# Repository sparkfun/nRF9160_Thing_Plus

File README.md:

SparkFun nRF9160 Thing Plus
========================================

[*SparkFun nRF9160 Thing Plus (17354)*](https://www.sparkfun.com/products/17354)

SparkFun has paired up with CircuitDojo to bring you the SparkFun nRF9160 Thing Plus, which features the powerful Nordic nRF9160 microcontroller in a feather-compatible footprint. This little chip is capable of both CAT M1 LTE and NB-IoT cellular communication and is designed to work with Zephyr, the go-to RTOS for embedded development.

Not only can you take advantage of Nordic’s advanced power states, but you can also put the device into a low power standby state. Laboratory measurements are putting that mode at about 2µA of current. 2µA! It also features a 3.3V Buck-Boost which helps get every mWh from your batteries as possible.

No batteries? No problem! You can plug or power your nRF9160 Thing Plus externally for AC/DC powered operation. Keep it on at all times for high availability scenarios. Power it the 5V pin or insert a micro-USB cable to keep things going.

Want to persist data? The nRF9160 Thing Plus has a 4MB external flash for storing data while offline. Using external flash with a filesystem like LitteFS and you’ll have a project to recon with!

Repository Contents
-------------------

* **/Hardware** - Eagle design files (.brd, .sch)
* **/Production** - Production panel files (.brd)

Documentation
--------------
* **[Hookup Guide](https://learn.sparkfun.com/tutorials/nrf9160-thing-plus-hookup-guide)** - Basic hookup guide for the SparkFun nRF9160 Thing Plus.

License Information
-------------------

This product is _**open source**_! 

Please review the LICENSE.md file for license information. 

If you have any questions or concerns on licensing, please contact technical support on our [SparkFun forums](https://forum.sparkfun.com/viewforum.php?f=152).

Distributed as-is; no warranty is given.

- Your friends at SparkFun.

_Designed in collaboration with [Jared Wolff](https://www.jaredwolff.com/) over at Circuit Dojo._

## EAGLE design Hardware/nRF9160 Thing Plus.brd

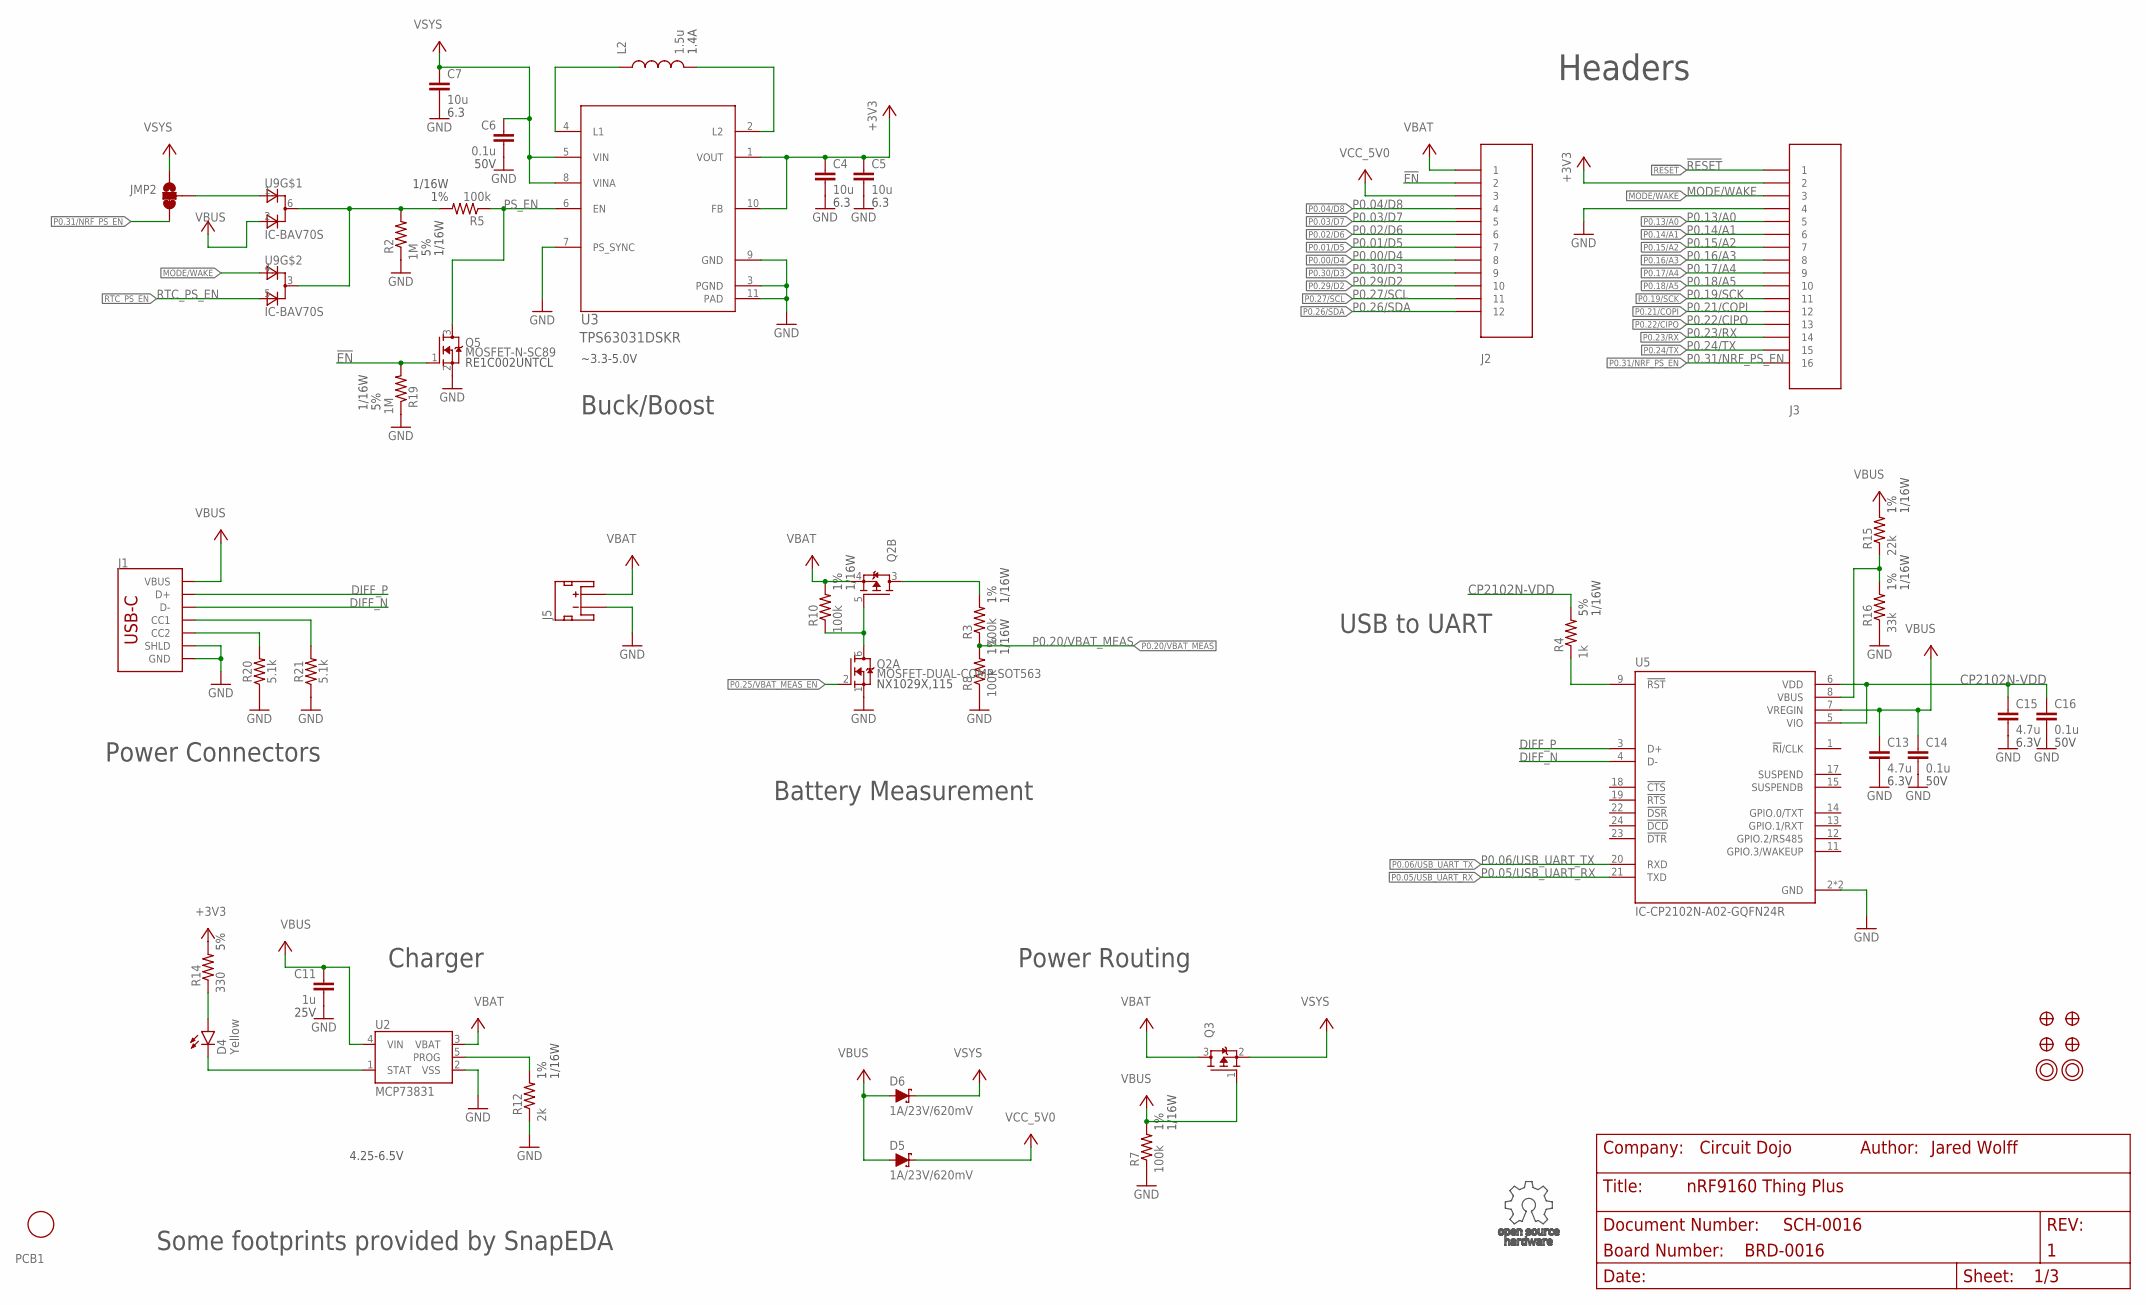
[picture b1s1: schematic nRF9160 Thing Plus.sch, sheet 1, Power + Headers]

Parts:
C4, C5, C7: 10u; C0603
C6, C14, C16: 0.1u; CAPC1005X55N
C11: 1u; CAPC1005X55N
C13, C15: 4.7u; C0603
D4: Yellow; LED-0603
D5, D6: 1A/23V/620mV; SOD-323
J1: USB Female C; USB-C-16P_4LAYER-PADS
J2: CON-HEADER-1X12-MALE-PIN
J3: CON-HEADER-1X16-MALE-PIN
J5: JST_2MM_MALE; JST-2-SMD
JMP2: JUMPER-3/1; JUMPER-ROUND-3-NO-R
L2: 1.5u; IND-2P0X2P0X1P2
PCB1: PCB-NRF91-FEATHER; PLACEHOLDER
Q2: MOSFET-DUAL-COMP-SOT563; SOT50P160X60-6N
Q3: MOSFET-P-20V-4.7A-SOT23; SOT23
Q5: MOSFET-N-SC89; DIO_RB558WMF-L
R2, R19: 1M; R0402-M
R3, R5, R7, R8, R10: 100k; R0402-M
R4: 1k; R0402-M
R12: 2k; R0402-M
R14: 330; R0402-M
R15: 22k; R0402-M
R16: 33k; R0402-M
R20, R21: 5.1k; 0402-TIGHT
U2: MCP73831; SOT23-5
U3: IC-TPS63031DSKR; DSK0010A
U5: IC-CP2102N-A02-GQFN24R; QFN50P400X400X80-25N
U9: IC-BAV70S; SOT363
U$3, U$4, U$24, U$35: FIDUCIAL-1MM
U$31, U$32: MOUNTING-HOLE-2.5MM-PLATED

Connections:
!EN: J2.2, Q5.1 (G), R19.2
!RESET: J3.1; also elsewhere on the board
+3V3: C4.1, C5.1, J3.2, R14.2, U3.1 (VOUT), U3.10 (FB); also elsewhere on the board
CHRG: D4.C, U2.1 (STAT)
CP212_VBUS: R15.1, R16.2, U5.8 (VBUS)
CP2102N-!RST: R4.1, U5.9 (!RST)
CP2102N-VDD: C15.1, C16.1, R4.2, U5.5 (VIO), U5.6 (VDD)
DIFF_N: J1.A7 (D-), J1.B7 (D-), U5.4 (D-)
DIFF_P: J1.A6 (D+), J1.B6 (D+), U5.3 (D+)
GND: C4.2, C5.2, C6.2, C7.2, C11.2, C13.2, C14.2, C15.2, C16.2, J1.GND, J1.GND2 (GND), J1.SHLD1 (SHLD), J1.SHLD2 (SHLD), J1.SHLD3 (SHLD), J1.SHLD4 (SHLD), J3.4, J5.1 (-), Q2.1 (S), Q5.2 (S), R2.1, R7.1, R8.1, R12.1, R16.1, R19.1, R20.1, R21.1, U2.2 (VSS), U3.3 (PGND), U3.7 (PS_SYNC), U3.9 (GND), U3.11 (PAD), U5.2 (GND), U5.25 (GND); also elsewhere on the board
MODE/WAKE: J3.3, U9.4 (A1); also elsewhere on the board
unnamed: L2.P$1 (1), U3.4 (L1)
unnamed: L2.P$2 (2), U3.2 (L2)
unnamed: J1.A5 (CC1), R21.2
unnamed: Q2.3 (D), R3.2
unnamed: Q2.5 (G), Q2.6 (D), R10.1
unnamed: J1.B5 (CC2), R20.2
unnamed: D4.A, R14.1
NRF_PS_EN_JMP: JMP2.P$2 (2), U9.1 (A1)
P0.00/D4: J2.8; also elsewhere on the board
P0.01/D5: J2.7; also elsewhere on the board
P0.02/D6: J2.6; also elsewhere on the board
P0.03/D7: J2.5; also elsewhere on the board
P0.04/D8: J2.4; also elsewhere on the board
P0.05/USB_UART_RX: U5.21 (TXD); also elsewhere on the board
P0.06/USB_UART_TX: U5.20 (RXD); also elsewhere on the board
P0.13/A0: J3.5; also elsewhere on the board
P0.14/A1: J3.6; also elsewhere on the board
P0.15/A2: J3.7; also elsewhere on the board
P0.16/A3: J3.8; also elsewhere on the board
P0.17/A4: J3.9; also elsewhere on the board
P0.18/A5: J3.10; also elsewhere on the board
P0.19/SCK: J3.11; also elsewhere on the board
P0.20/VBAT_MEAS: R3.1, R8.2; also elsewhere on the board
P0.21/COPI: J3.12; also elsewhere on the board
P0.22/CIPO: J3.13; also elsewhere on the board
P0.23/RX: J3.14; also elsewhere on the board
P0.24/TX: J3.15; also elsewhere on the board
P0.25/VBAT_MEAS_EN: Q2.2 (G); also elsewhere on the board
P0.26/SDA: J2.12; also elsewhere on the board
P0.27/SCL: J2.11; also elsewhere on the board
P0.29/D2: J2.10; also elsewhere on the board
P0.30/D3: J2.9; also elsewhere on the board
P0.31/NRF_PS_EN: J3.16, JMP2.P$3 (3); also elsewhere on the board
PROG: R12.2, U2.5 (PROG)
PS_EN: Q5.3 (D), R5.1, U3.6 (EN)
PS_EN_CC: R2.2, R5.2, U9.3 (C), U9.6 (C)
RTC_PS_EN: U9.5 (A2); also elsewhere on the board
VBAT: J2.1, J5.2 (+), Q2.4 (S), Q3.3 (D), R10.2, U2.3 (VBAT)
VBUS: C11.1, C13.1, C14.1, D5.A, D6.A, J1.VBUS1 (VBUS), J1.VBUS2 (VBUS), Q3.1 (G), R7.2, R15.2, U2.4 (VIN), U5.7 (VREGIN), U9.2 (A2)
VCC_5V0: D5.C, J2.3
VSYS: C6.1, C7.1, D6.C, JMP2.P$1 (1), Q3.2 (S), U3.5 (VIN), U3.8 (VINA); also elsewhere on the board

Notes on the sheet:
Headers
Some footprints provided by SnapEDA
Buck/Boost
Power Routing
Battery Measurement
Charger
USB to UART
Power Connectors
4.25-6.5V
~3.3-5.0V

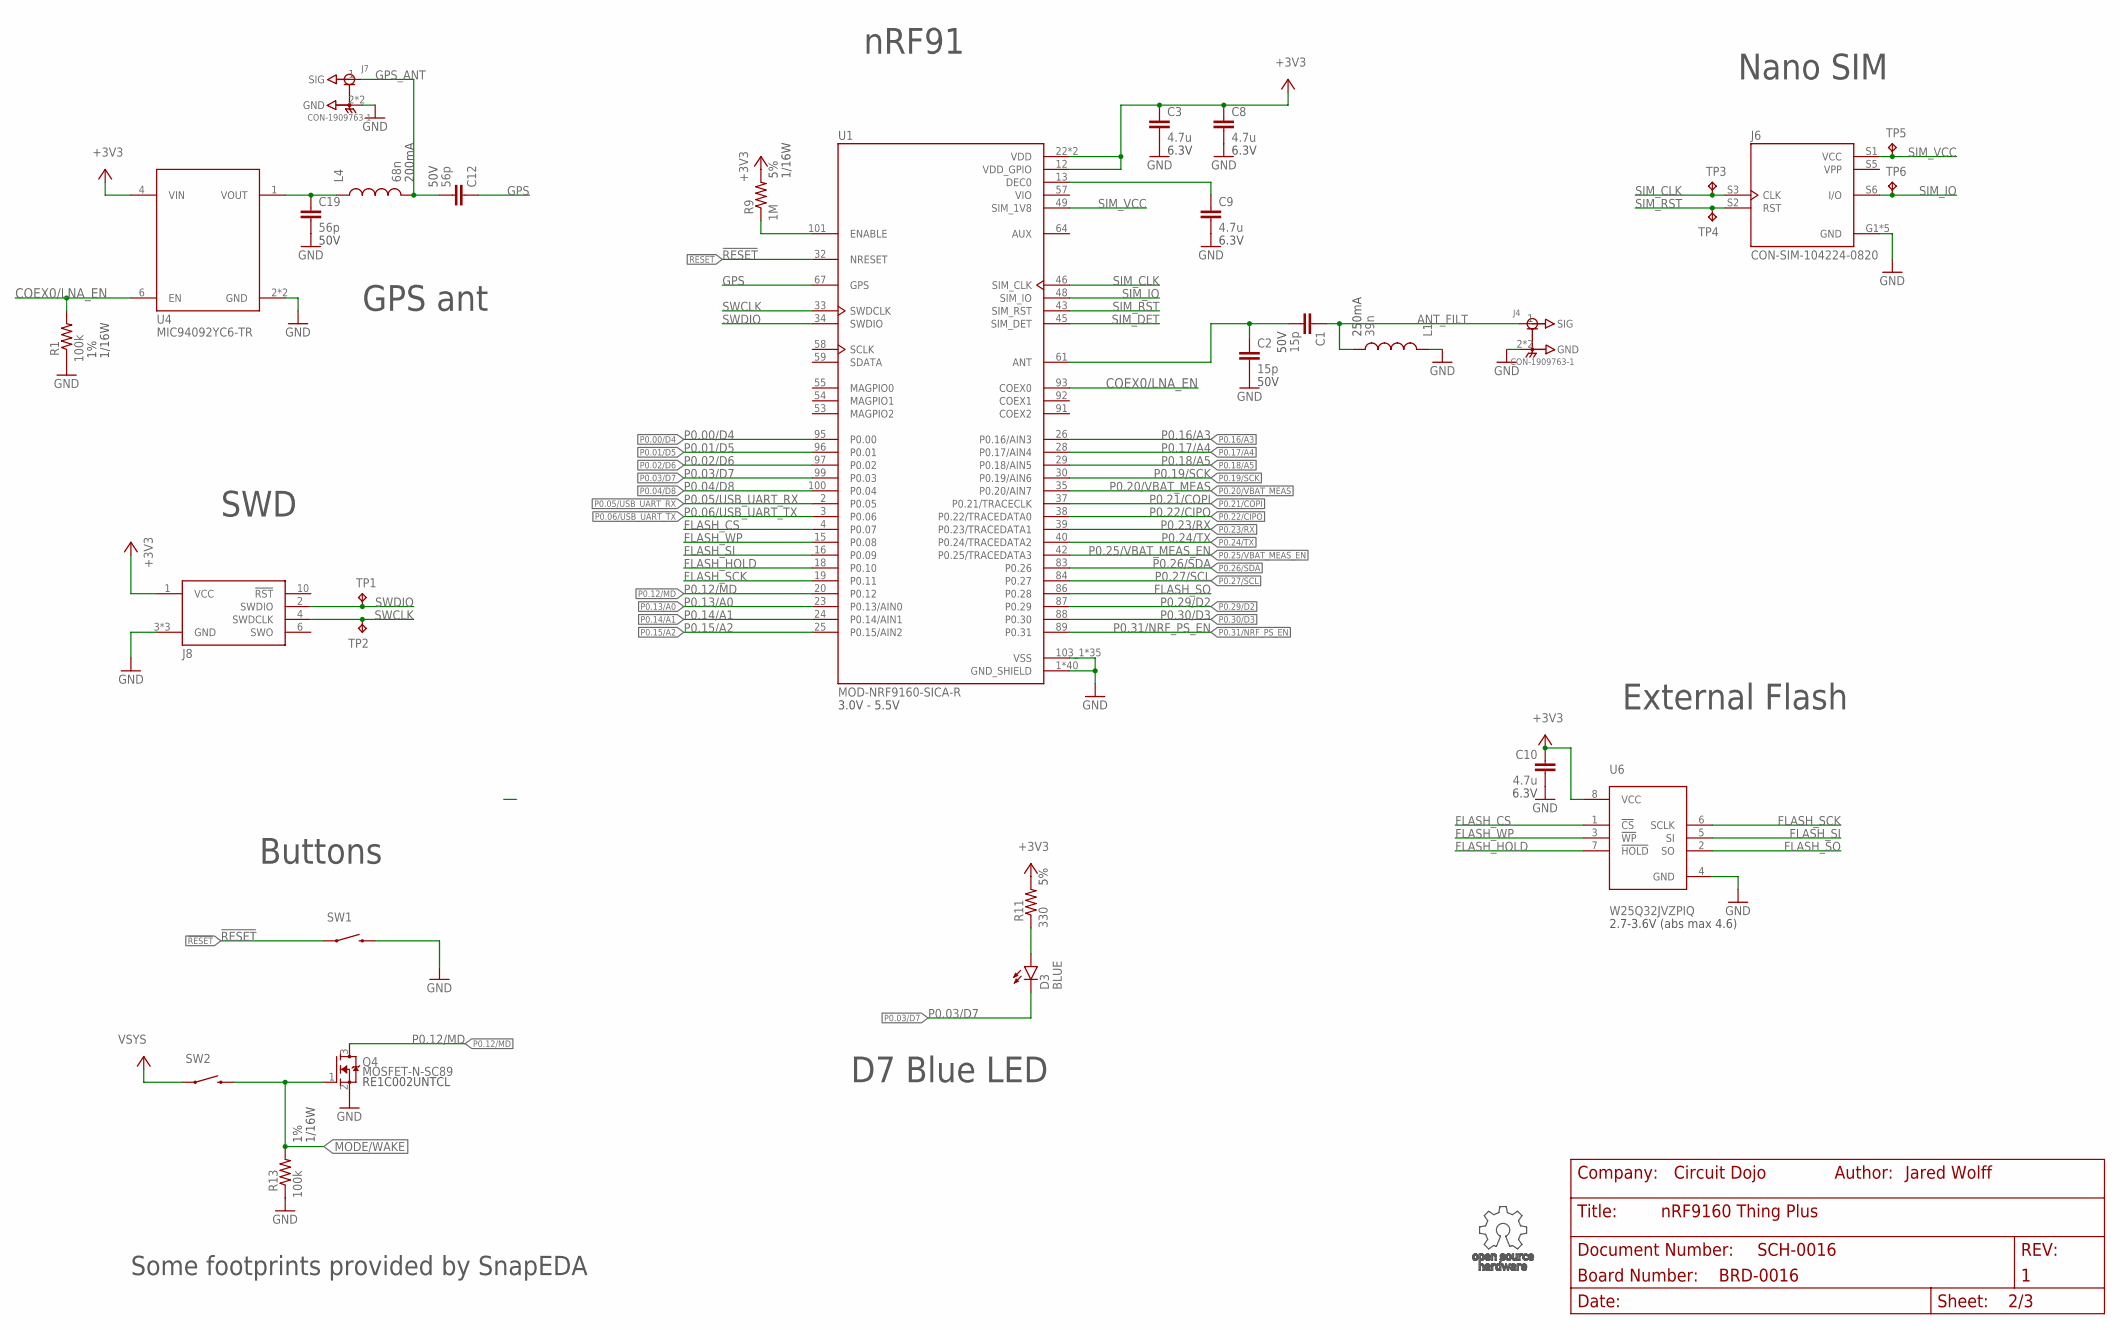
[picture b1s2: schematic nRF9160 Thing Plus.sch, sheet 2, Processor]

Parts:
C1, C2: 15p; CAPC1005X55N
C3, C8, C9, C10: 4.7u; C0603
C12, C19: 56p; CAPC1005X55N
D3: BLUE; LED-0603
J4, J7: CON-1909763-1; TE_1909763-1
J6: CON-SIM-104224-0820; MOLEX_104224-0820
J8: CON-FTSH-105-XX-X-DV; SAMTEC_FTSH-105-XX-X-DV
L1: 39n; IND0402_22N_TAI
L4: 68n; IND0402_22N_TAI
Q4: MOSFET-N-SC89; DIO_RB558WMF-L
R1, R13: 100k; R0402-M
R9: 1M; R0402-M
R11: 330; R0402-M
SW1, SW2: MOMENTARY-SWITCH-SPST-SMD-4.6X2.8MM; TACTILE_SWITCH_SMD_4.6X2.8MM
TP1, TP2, TP3, TP4, TP5, TP6: TP-1SIDE-1P0; TP-1P0
U1: MOD-NRF9160-SICA-R; NORDIC_NRF9160-SICA-R
U4: POWER-SWITCH-MIC94092YC6; SOT363
U6: FLASH-WSON; WIN_ZP-8-L

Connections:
!RESET: SW1.1, SW1.2 (1), U1.32 (NRESET); also elsewhere on the board
+3V3: C3.1, C8.1, C10.1, J8.1 (VCC), R9.2, R11.2, U1.12 (VDD_GPIO), U1.22 (VDD), U1.102 (VDD), U4.4 (VIN), U6.8 (VCC); also elsewhere on the board
ANT: C1.2, C2.1, U1.61 (ANT)
ANT_FILT: C1.1, J4.1 (SIG), L1.2
COEX0/LNA_EN: R1.2, U1.93 (COEX0), U4.6 (EN)
FLASH_CS: U1.4 (P0.07), U6.1 (!CS)
FLASH_HOLD: U1.18 (P0.10), U6.7 (!HOLD)
FLASH_SCK: U1.19 (P0.11), U6.6 (SCLK)
FLASH_SI: U1.16 (P0.09), U6.5 (SI)
FLASH_SO: U1.86 (P0.28), U6.2 (SO)
FLASH_WP: U1.15 (P0.08), U6.3 (!WP)
GND: C2.2, C3.2, C8.2, C9.2, C10.2, C19.2, J4.2 (GND), J4.3 (GND), J6.G1 (GND), J6.G2 (GND), J6.G3 (GND), J6.G4 (GND), J6.S4 (GND), J7.2 (GND), J7.3 (GND), J8.3 (GND), J8.5 (GND), J8.9 (GND), L1.1, Q4.2 (S), R1.1, R13.1, SW1.3 (2), SW1.4 (2), U1.1 (GND_SHIELD), U1.5 (GND_SHIELD), U1.6 (GND_SHIELD), U1.7 (GND_SHIELD), U1.8 (GND_SHIELD), U1.9 (GND_SHIELD), U1.11 (GND_SHIELD), U1.14 (GND_SHIELD), U1.17 (GND_SHIELD), U1.21 (GND_SHIELD), U1.27 (GND_SHIELD), U1.31 (GND_SHIELD), U1.36 (GND_SHIELD), U1.41 (GND_SHIELD), U1.44 (GND_SHIELD), U1.47 (GND_SHIELD), U1.50 (GND_SHIELD), U1.52 (GND_SHIELD), U1.56 (GND_SHIELD), U1.60 (GND_SHIELD), U1.62 (GND_SHIELD), U1.63 (GND_SHIELD), U1.65 (GND_SHIELD), U1.66 (GND_SHIELD), U1.68 (GND_SHIELD), U1.69 (GND_SHIELD), U1.72 (GND_SHIELD), U1.74 (GND_SHIELD), U1.75 (GND_SHIELD), U1.76 (GND_SHIELD), U1.77 (GND_SHIELD), U1.78 (GND_SHIELD), U1.79 (GND_SHIELD), U1.80 (GND_SHIELD), U1.81 (GND_SHIELD), U1.82 (GND_SHIELD), U1.85 (GND_SHIELD), U1.90 (GND_SHIELD), U1.94 (GND_SHIELD), U1.98 (GND_SHIELD), U1.103_1 (VSS), U1.103_2 (VSS), U1.103_3 (VSS), U1.103_4 (VSS), U1.103_5 (VSS), U1.103_6 (VSS), U1.103_7 (VSS), U1.103_8 (VSS), U1.103_9 (VSS), U1.103_10 (VSS), U1.103_11 (VSS), U1.103_12 (VSS), U1.103_13 (VSS), U1.103_14 (VSS), U1.103_15 (VSS), U1.103_16 (VSS), U1.103_17 (VSS), U1.103_18 (VSS), U1.103_19 (VSS), U1.103_20 (VSS), U1.103_21 (VSS), U1.103_22 (VSS), U1.103_23 (VSS), U1.103_24 (VSS), U1.103_25 (VSS), U1.103_26 (VSS), U1.103_27 (VSS), U1.103_28 (VSS), U1.103_29 (VSS), U1.103_30 (VSS), U1.103_31 (VSS), U1.103_32 (VSS), U1.103_33 (VSS), U1.103_34 (VSS), U1.103_35 (VSS), U4.2 (GND), U4.5 (GND), U6.4 (GND); also elsewhere on the board
GPS: C12.1, U1.67 (GPS)
GPS_ANT: C12.2, J7.1 (SIG), L4.2
LNA_SW_OUT: C19.1, L4.1, U4.1 (VOUT)
MODE/WAKE: Q4.1 (G), R13.2, SW2.3 (2), SW2.4 (2); also elsewhere on the board
unnamed: R9.1, U1.101 (ENABLE)
unnamed: C9.1, U1.13 (DEC0)
unnamed: D3.A, R11.1
P0.00/D4: U1.95 (P0.00); also elsewhere on the board
P0.01/D5: U1.96 (P0.01); also elsewhere on the board
P0.02/D6: U1.97 (P0.02); also elsewhere on the board
P0.03/D7: D3.C, U1.99 (P0.03); also elsewhere on the board
P0.04/D8: U1.100 (P0.04); also elsewhere on the board
P0.05/USB_UART_RX: U1.2 (P0.05); also elsewhere on the board
P0.06/USB_UART_TX: U1.3 (P0.06); also elsewhere on the board
P0.12/MD: Q4.3 (D), U1.20 (P0.12)
P0.13/A0: U1.23 (P0.13/AIN0); also elsewhere on the board
P0.14/A1: U1.24 (P0.14/AIN1); also elsewhere on the board
P0.15/A2: U1.25 (P0.15/AIN2); also elsewhere on the board
P0.16/A3: U1.26 (P0.16/AIN3); also elsewhere on the board
P0.17/A4: U1.28 (P0.17/AIN4); also elsewhere on the board
P0.18/A5: U1.29 (P0.18/AIN5); also elsewhere on the board
P0.19/SCK: U1.30 (P0.19/AIN6); also elsewhere on the board
P0.20/VBAT_MEAS: U1.35 (P0.20/AIN7); also elsewhere on the board
P0.21/COPI: U1.37 (P0.21/TRACECLK); also elsewhere on the board
P0.22/CIPO: U1.38 (P0.22/TRACEDATA0); also elsewhere on the board
P0.23/RX: U1.39 (P0.23/TRACEDATA1); also elsewhere on the board
P0.24/TX: U1.40 (P0.24/TRACEDATA2); also elsewhere on the board
P0.25/VBAT_MEAS_EN: U1.42 (P0.25/TRACEDATA3); also elsewhere on the board
P0.26/SDA: U1.83 (P0.26); also elsewhere on the board
P0.27/SCL: U1.84 (P0.27); also elsewhere on the board
P0.29/D2: U1.87 (P0.29); also elsewhere on the board
P0.30/D3: U1.88 (P0.30); also elsewhere on the board
P0.31/NRF_PS_EN: U1.89 (P0.31); also elsewhere on the board
SIM_CLK: J6.S3 (CLK), TP3.TP, U1.46 (SIM_CLK)
SIM_DET: U1.45 (SIM_DET)
SIM_IO: J6.S6 (I/O), TP6.TP, U1.48 (SIM_IO)
SIM_RST: J6.S2 (RST), TP4.TP, U1.43 (SIM_RST)
SIM_VCC: J6.S1 (VCC), TP5.TP, U1.49 (SIM_1V8)
SWCLK: J8.4 (SWDCLK), TP2.TP, U1.33 (SWDCLK)
SWDIO: J8.2 (SWDIO), TP1.TP, U1.34 (SWDIO)
VIO: U1.57 (VIO)
VPP: J6.S5 (VPP)
VSYS: SW2.1, SW2.2 (1); also elsewhere on the board

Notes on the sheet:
Some footprints provided by SnapEDA
nRF91
SWD
Buttons
External Flash
D7 Blue LED
3.0V - 5.5V
2.7-3.6V (abs max 4.6)
GPS ant
Nano SIM

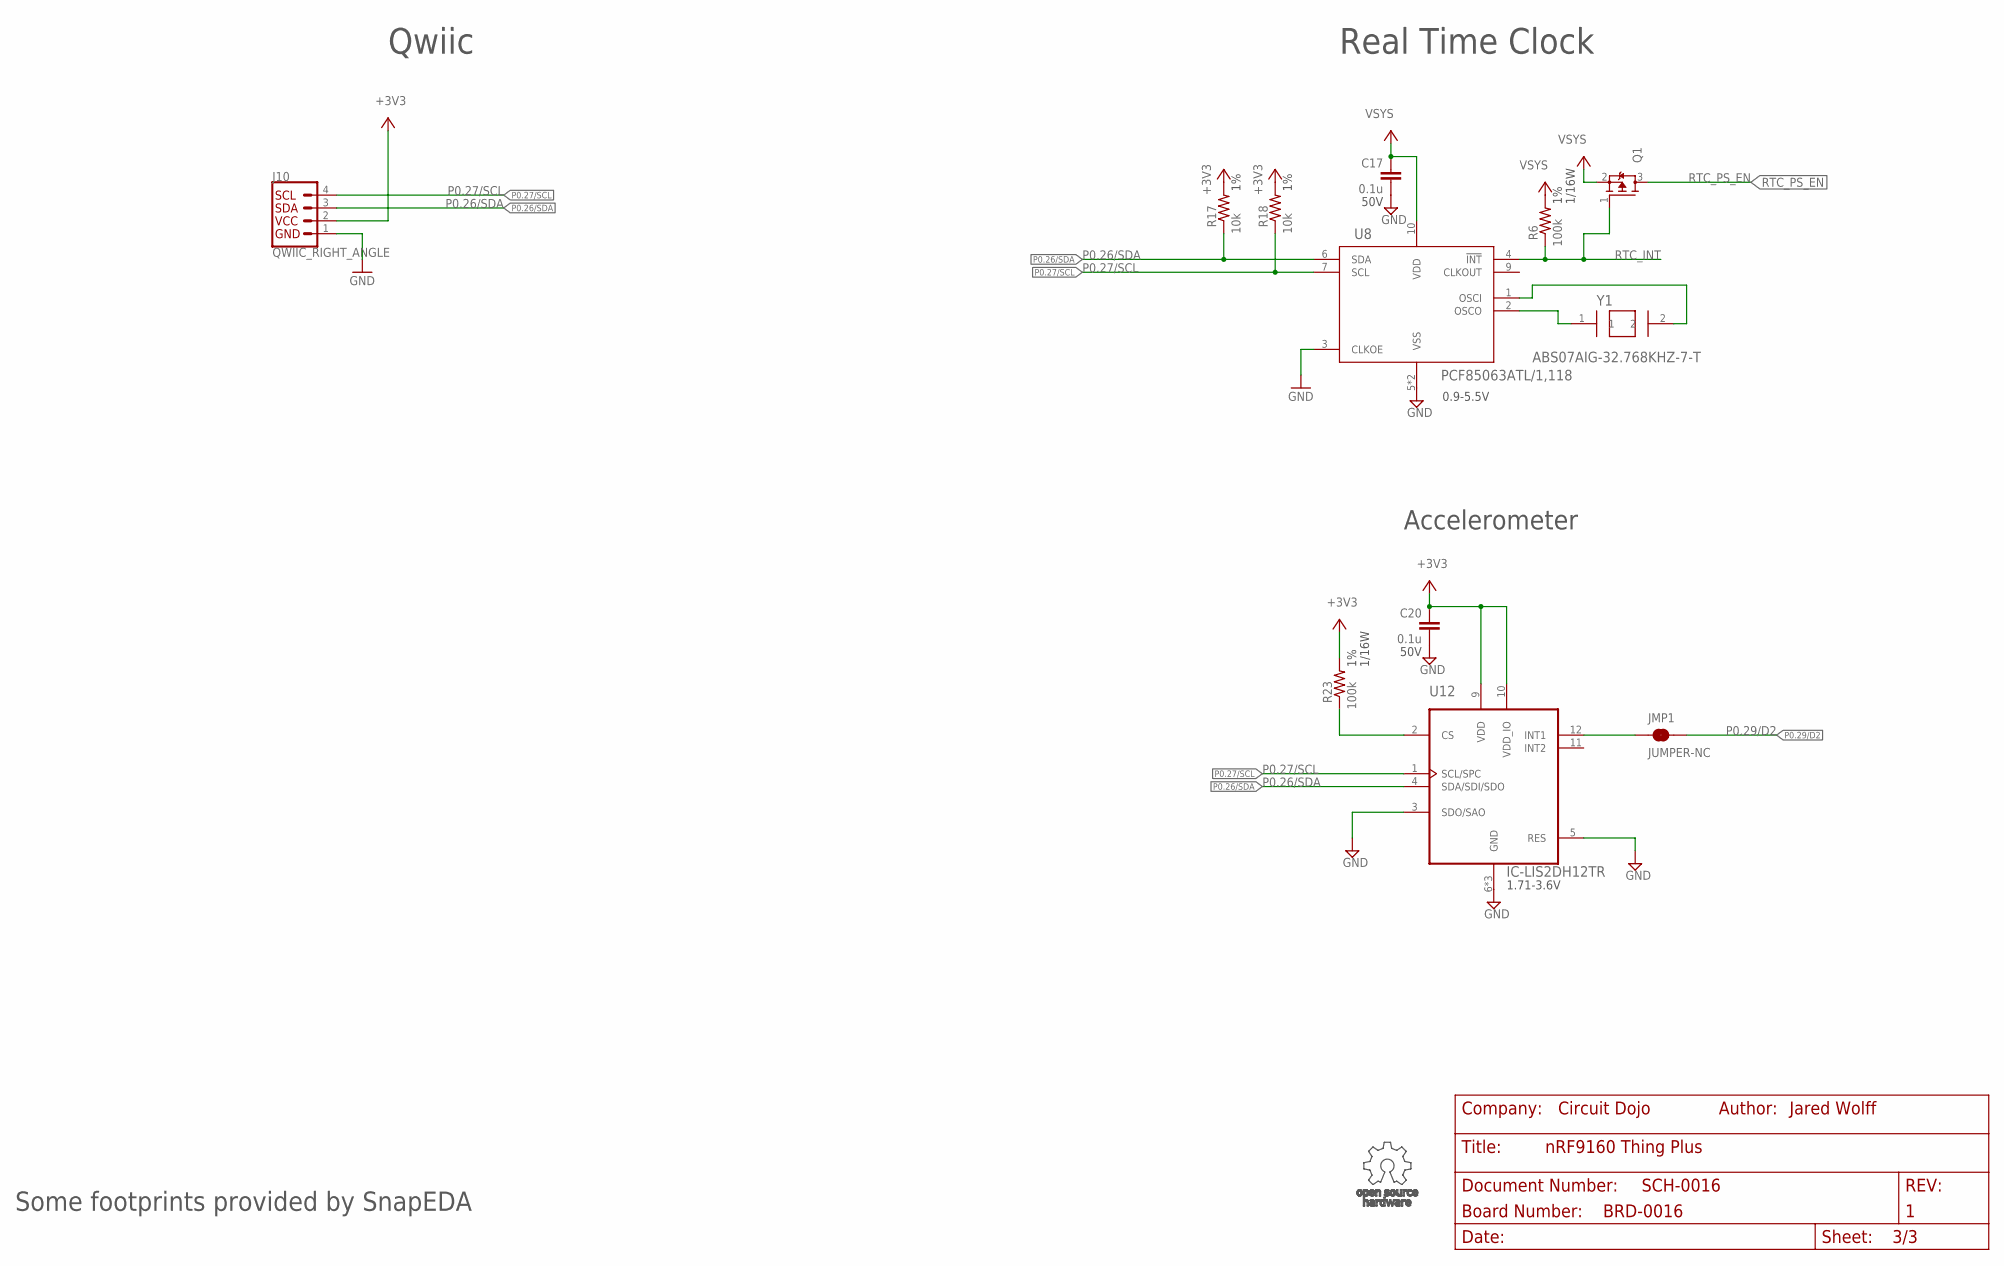
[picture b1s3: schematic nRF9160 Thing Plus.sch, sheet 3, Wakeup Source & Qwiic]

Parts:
C17, C20: 0.1u; CAPC1005X55N
J10: QWIIC_RIGHT_ANGLE; JST04_1MM_RA
JMP1: JUMPER-NC; JUMPER-ROUND-NC
Q1: MOSFET-P-SC89; DIO_RB558WMF-L
R6, R23: 100k; R0402-M
R17, R18: 10k; R0402-M
U8: IC-PCF85063ATL/1; DFN10_2P7X2P7-L
U12: IC-LIS2DH12TR; PQFN50P200X200100-12N
Y1: XTAL-ABS07AIG-32.768KHZ-7-T; XTAL320X150X90

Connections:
+3V3: C20.1, J10.2, R17.2, R18.2, R23.2, U12.9 (VDD), U12.10 (VDD_IO); also elsewhere on the board
GND: C17.2, C20.2, J10.1, U8.3 (CLKOE), U8.5 (VSS), U8.11 (VSS), U12.3 (SDO/SAO), U12.5 (RES), U12.6 (GND), U12.7 (GND), U12.8 (GND); also elsewhere on the board
unnamed: U8.1 (OSCI), Y1.2
unnamed: R23.1, U12.2 (CS)
unnamed: JMP1.P$1 (1), U12.12 (INT1)
unnamed: U8.2 (OSCO), Y1.1
P0.26/SDA: J10.3, R17.1, U8.6 (SDA), U12.4 (SDA/SDI/SDO); also elsewhere on the board
P0.27/SCL: J10.4, R18.1, U8.7 (SCL), U12.1 (SCL/SPC); also elsewhere on the board
P0.29/D2: JMP1.P$2 (2); also elsewhere on the board
RTC_INT: Q1.1 (G), R6.1, U8.4 (!INT)
RTC_PS_EN: Q1.3 (D); also elsewhere on the board
VSYS: C17.1, Q1.2 (S), R6.2, U8.10 (VDD); also elsewhere on the board

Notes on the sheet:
Some footprints provided by SnapEDA
Real Time Clock
0.9-5.5V
Qwiic
Accelerometer
1.71-3.6V

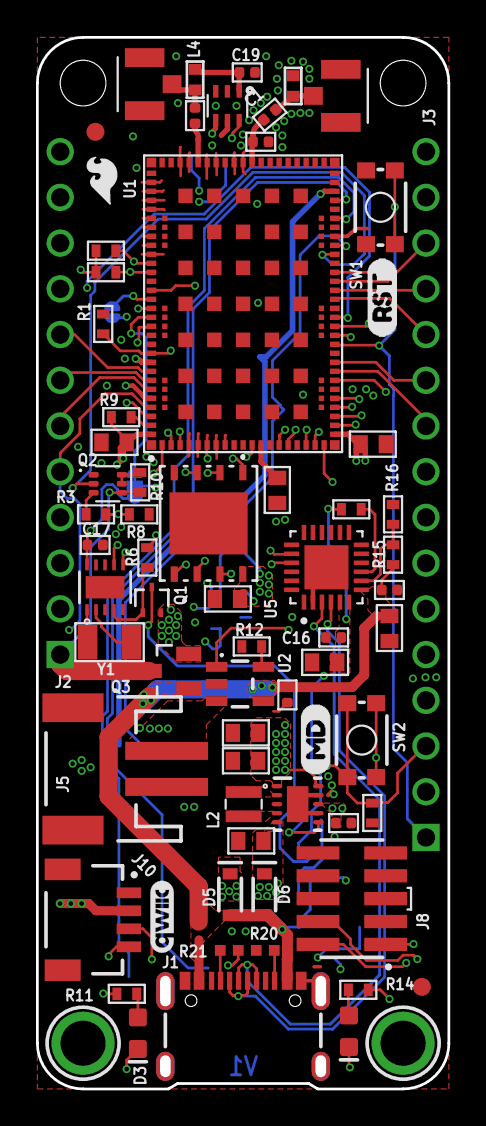
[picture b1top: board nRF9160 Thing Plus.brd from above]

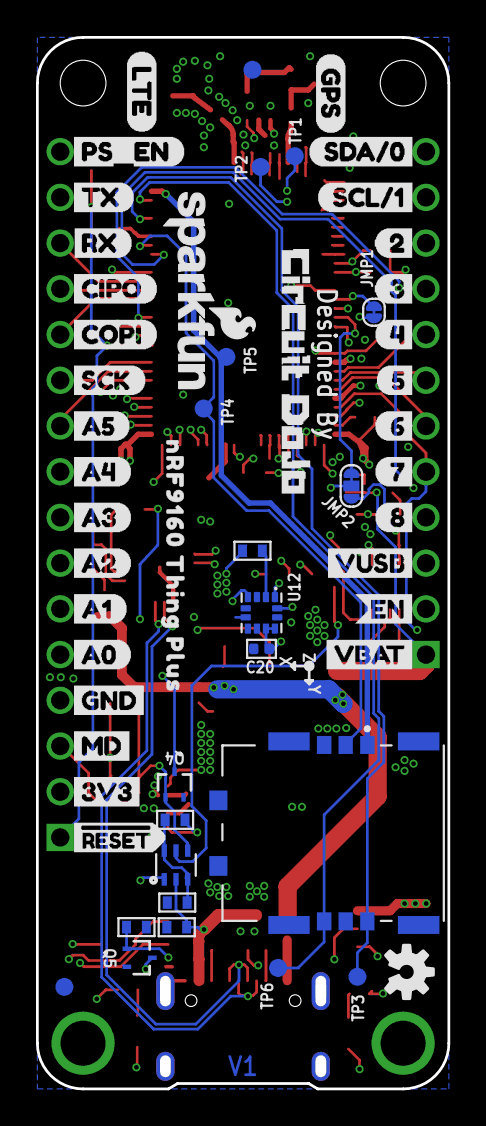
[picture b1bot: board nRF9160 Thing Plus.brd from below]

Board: 4 copper layers, 22.9 x 58.4 mm, 128 parts (55 on the bottom side), 79 nets.

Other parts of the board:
LOGO5: OSHW-LOGOS; OSHW-LOGO-S
U$1: SFE_LOGO_NAME_FLAME_.1
U$2: LOGO-CIRCUITDOJO
U$5: A3L-LOC
U$6: QWIIC_4MM
U$7: RST0
U$8: PS_EN0
U$9, U$14: MD0
U$10: 20
U$11: 30
U$12: SCL#11
U$13: SDA#00
U$15: SFE_LOGO_FLAME_.1
U$16: TX0
U$17: RX0
U$18: SCK0
U$19: CIPO0
U$20: COPI0
U$21: GPS0
U$22: LTE0
U$23: NRF9160_THING_PLUS0
U$69: GND12
U$71: 3V314
U$72: #RESET15
U$73: VUSB25
U$74: EN26
U$75: VBAT27
U$83: A56
U$84: A47
U$85: A38
U$86: A29
U$87: A110
U$88: A011
U$89: 412
U$90: 513
U$91: 614
U$92: 715
U$93: 816

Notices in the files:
parts and their libraries:
SparkFun-Connectors: Licensing: Creative Commons ShareAlike 4.0 International - https://creativecommons.org/licenses/by-sa/4.0
